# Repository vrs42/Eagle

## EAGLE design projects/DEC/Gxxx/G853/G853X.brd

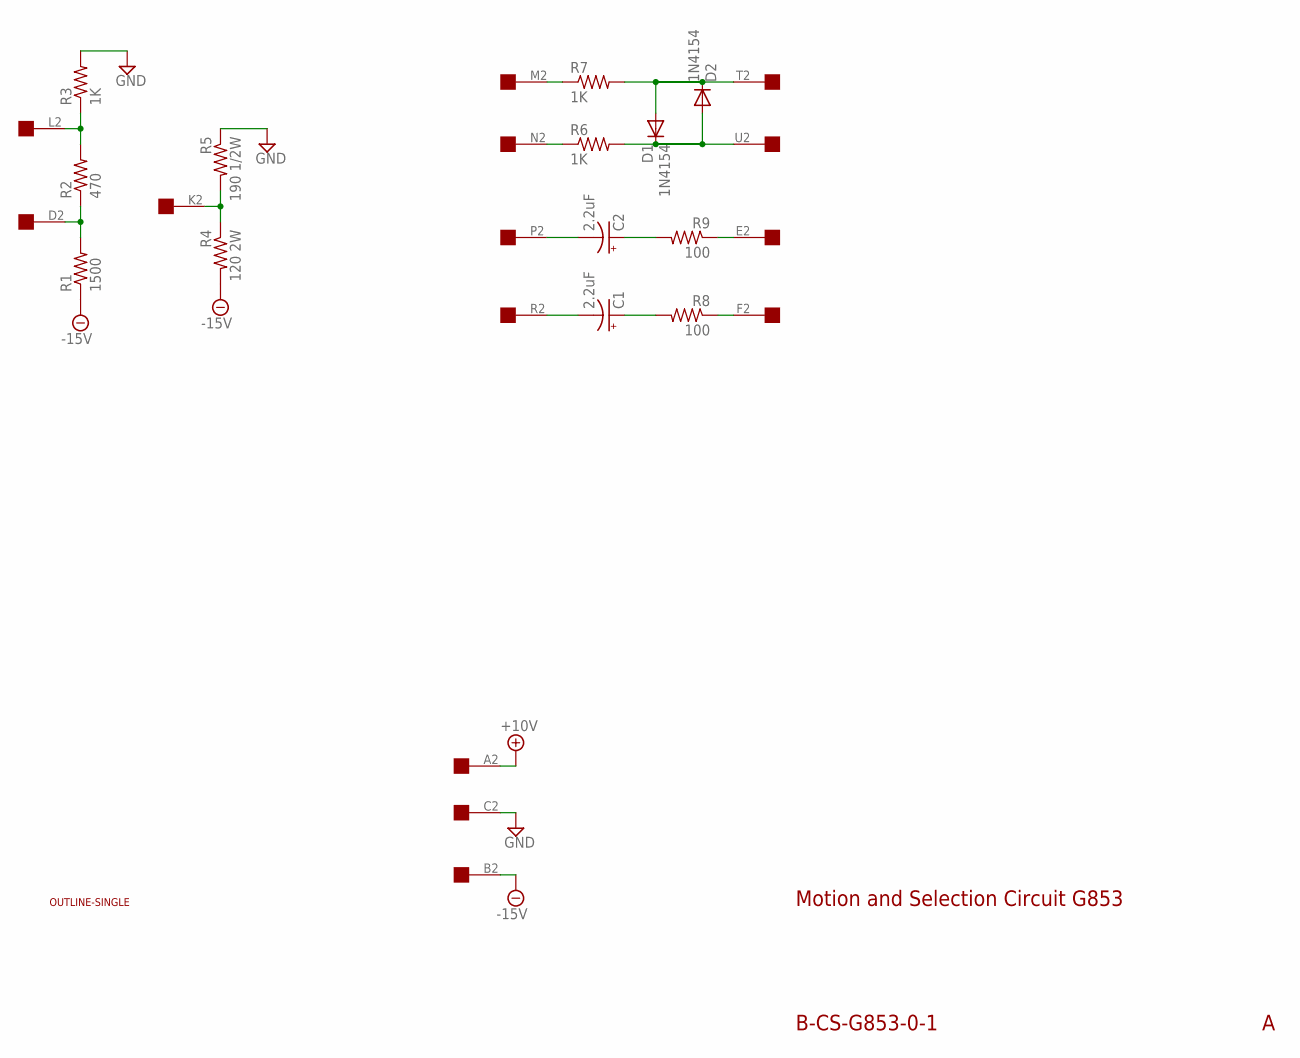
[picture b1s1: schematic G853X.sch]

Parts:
C1, C2: 2.2uF; E15-5
D1, D2: 1N4154; DO35-10
R1: 1500; 0207/10
R2: 470; 0207/10
R3, R6, R7: 1K; 0207/10
R4: 120 2W; P0817/22
R5: 190 1/2W; 0309/12
R8, R9: 100; 0207/10
U$1: OUTLINE-SINGLE; SINGLE
U$2: EDGE-1; EDGE-CON1

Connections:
+10V: U$2.A2
-15V: R1.1, R4.2, U$2.B2
GND: R3.2, R5.1, U$2.C2
unnamed: C1.-, U$2.R2
unnamed: C1.+, R8.2
unnamed: R1.2, R2.1, U$2.D2
unnamed: R6.1, U$2.N2
unnamed: R7.1, U$2.M2
unnamed: D1.A, D2.C, R7.2, U$2.T2
unnamed: D1.C, D2.A, R6.2, U$2.U2
unnamed: R2.2, R3.1, U$2.L2
unnamed: C2.+, R9.2
unnamed: C2.-, U$2.P2
unnamed: R8.1, U$2.F2
unnamed: R9.1, U$2.E2
unnamed: R4.1, R5.2, U$2.K2

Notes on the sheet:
Motion and Selection Circuit G853
B-CS-G853-0-1

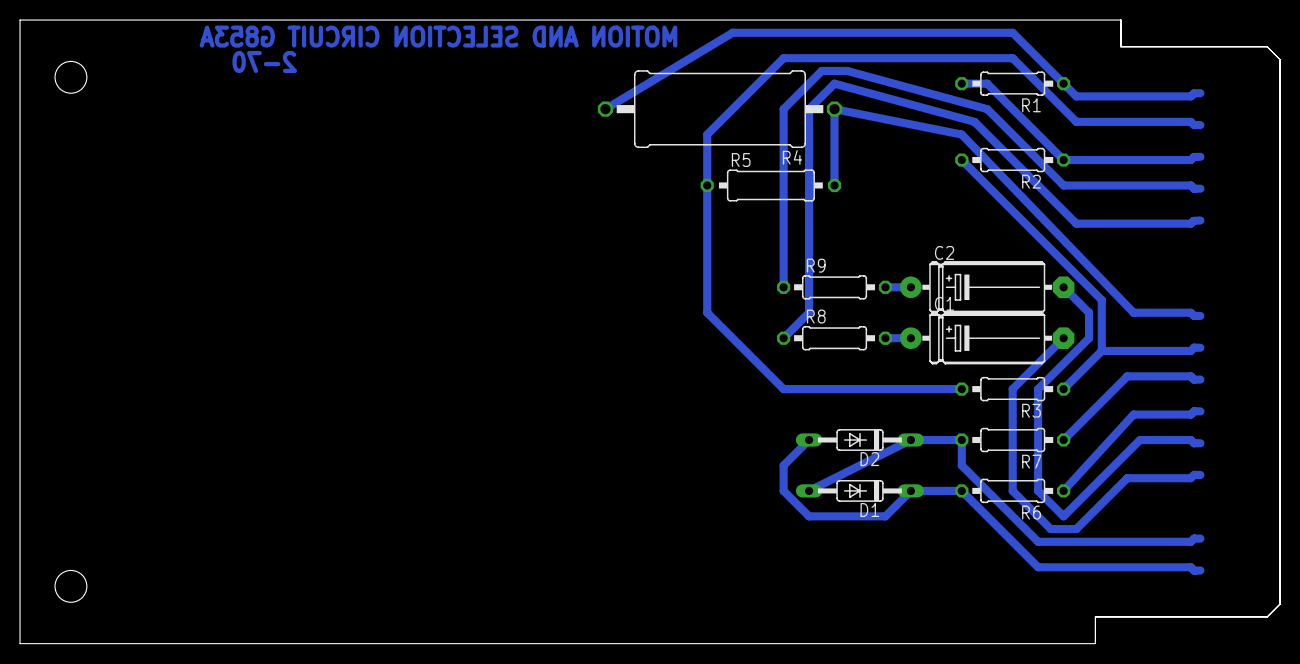
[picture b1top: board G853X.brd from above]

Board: 2 copper layers, 125.7 x 62.2 mm, 15 parts (0 on the bottom side), 15 nets.

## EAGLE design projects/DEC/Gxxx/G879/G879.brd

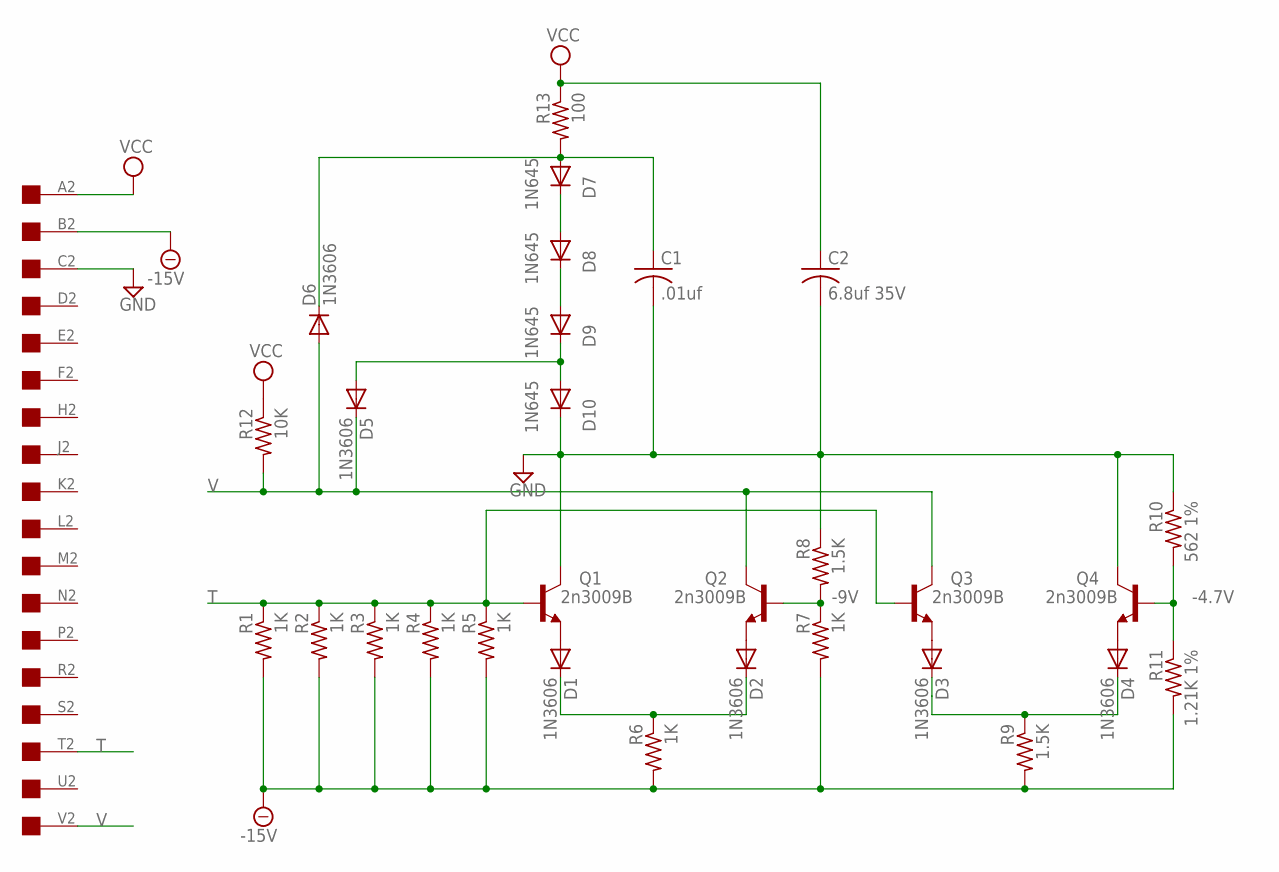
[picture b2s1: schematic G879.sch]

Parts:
C1: .01uf; C050-025X075
C2: 6.8uf 35V; C102-054X133
D1, D2, D3, D4, D5, D6: 1N3606; DO41-10
D7, D8, D9, D10: 1N645; DO41-10
Q1, Q2, Q3, Q4: 2n3009B; TO39
R1, R2, R3, R4, R5, R6, R7: 1K; 0207/10
R8, R9: 1.5K; 0207/10
R10: 562 1%; 0207/10
R11: 1.21K 1%; 0207/10
R12: 10K; 0207/10
R13: 100; 0207/10
U$5: ONE-SIDED

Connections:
-4.7V: Q4.2 (B), R10.2, R11.1
-9V: Q2.2 (B), R7.1, R8.2
-15V: R1.2, R2.2, R3.2, R4.2, R5.2, R6.2, R7.2, R9.2, R11.2, U$5.B2
GND: C1.2, C2.2, D10.C, Q1.3 (C), Q4.3 (C), R8.1, R10.1, U$5.C2
unnamed: D1.A, Q1.1 (E)
unnamed: D3.C, D4.C, R9.1
unnamed: D2.A, Q2.1 (E)
unnamed: D4.A, Q4.1 (E)
unnamed: D5.A, D9.C, D10.A
unnamed: D1.C, D2.C, R6.1
unnamed: D8.C, D9.A
unnamed: D3.A, Q3.1 (E)
unnamed: D7.C, D8.A
unnamed: C1.1, D6.C, D7.A, R13.2
T: Q1.2 (B), Q3.2 (B), R1.1, R2.1, R3.1, R4.1, R5.1, U$5.T2
V: D5.C, D6.A, Q2.3 (C), Q3.3 (C), R12.2, U$5.V2
VCC: C2.1, R12.1, R13.1, U$5.A2

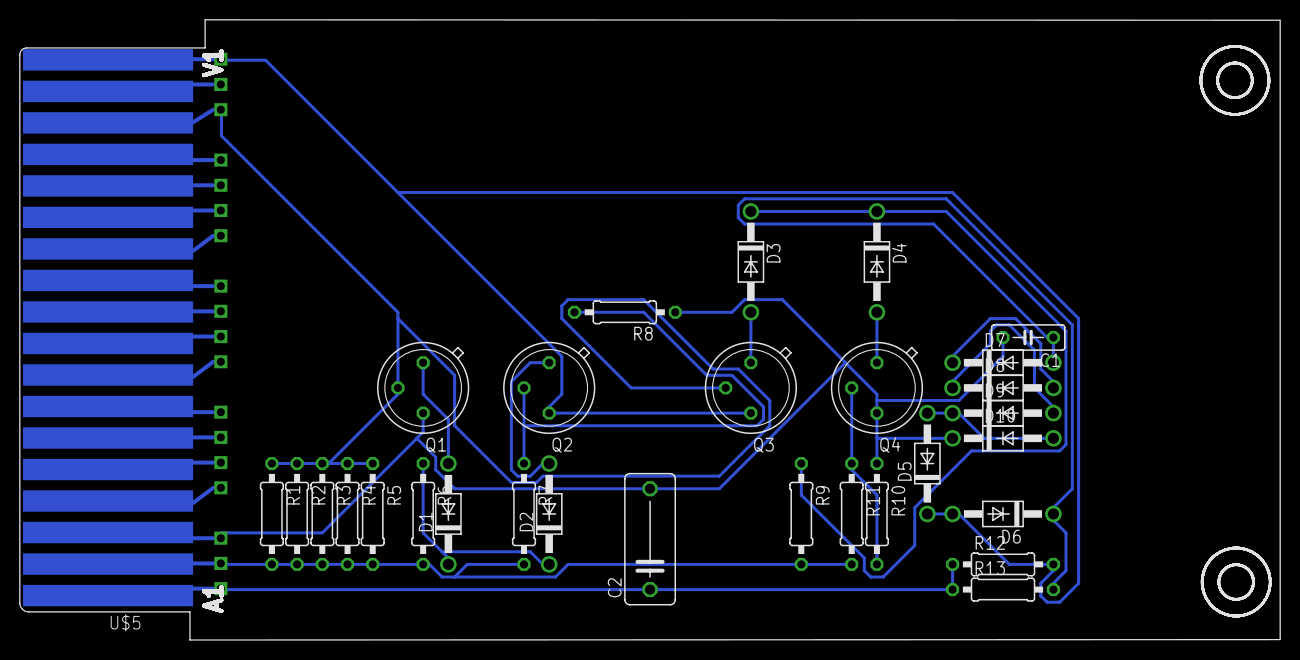
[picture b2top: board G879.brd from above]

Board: 2 copper layers, 127.0 x 62.5 mm, 32 parts (0 on the bottom side), 17 nets.

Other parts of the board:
U$2, U$3: 3,3

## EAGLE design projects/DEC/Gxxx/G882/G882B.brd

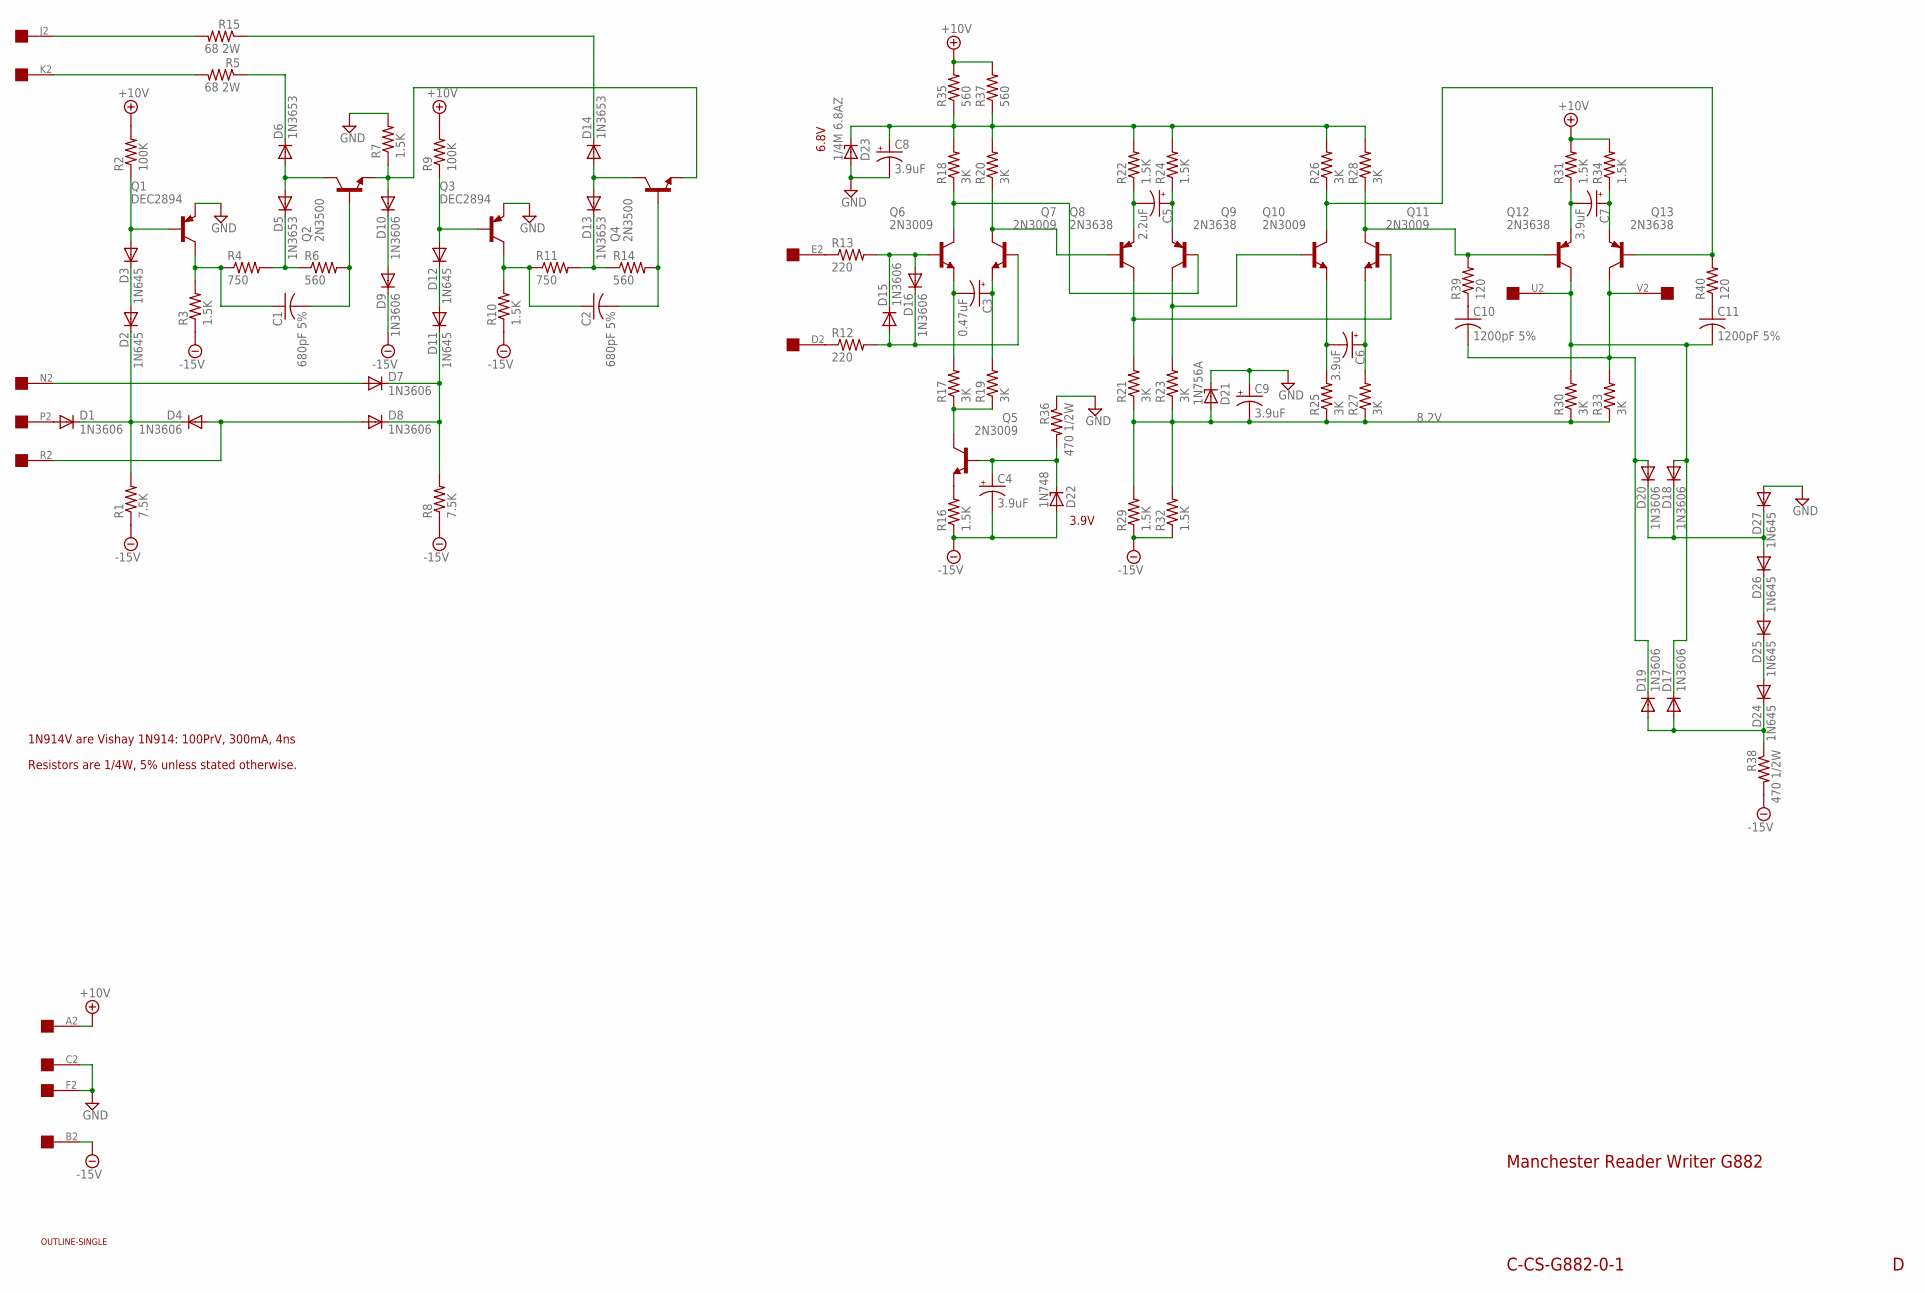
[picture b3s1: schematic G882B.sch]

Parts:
C1, C2: 680pF 5%; C050-025X075
C3: 0.47uF; E12-4
C4, C6, C7, C8, C9: 3.9uF; E12-4
C5: 2.2uF; E12-4
C10, C11: 1200pF 5%; C050-025X075
D1, D4, D7, D8, D9, D10, D15, D16, D17, D18, D19, D20: 1N3606; DO35-10
D2, D3, D11, D12, D24, D25, D26, D27: 1N645; DO35-10
D5, D6, D13, D14: 1N3653; DO35-10
D21: 1N756A; DO35Z10
D22: 1N748; DO35Z10
D23: 1/4M 6.8AZ; DO35Z10
Q1, Q3: DEC2894; TO39
Q2, Q4: 2N3500; TO5
Q5, Q6, Q7, Q10, Q11: 2N3009; TO5
Q8, Q9, Q12, Q13: 2N3638; TO39
R1, R8: 7.5K; 0207/10
R2, R9: 100K; 0207/10
R3, R7, R10, R16, R22, R24, R29, R31, R32, R34: 1.5K; 0207/10
R4, R11: 750; 0207/10
R5, R15: 68 2W; P0817/22
R6, R14, R35, R37: 560; 0207/10
R12, R13: 220; 0207/10
R17, R18, R19, R20, R21, R23, R25, R26, R27, R28, R30, R33: 3K; 0207/10
R36, R38: 470 1/2W; 0309/12
R39, R40: 120; 0207/10
U$1: OUTLINE-SINGLE; SINGLE
U$2: EDGE-1; EDGE-CON1

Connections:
8.2V: C9.-, D21.A, R21.1, R23.1, R25.1, R27.1, R29.2, R30.1, R32.2, R33.1
+10V: R2.2, R9.2, R31.2, R34.2, R35.2, R37.2, U$2.A2
-15V: C4.-, D9.C, D22.A, R1.1, R3.1, R8.1, R10.1, R16.1, R29.1, R32.1, R38.2, U$2.B2
GND: C8.-, C9.+, D21.C, D23.A, D27.A, Q1.1 (E), Q3.1 (E), R7.2, R36.1, U$2.C2, U$2.F2
unnamed: D1.A, U$2.P2
unnamed: D11.A, D12.C
unnamed: D4.A, D8.A, U$2.R2
unnamed: D7.A, U$2.N2
unnamed: C1.1, Q1.3 (C), R3.2, R4.1
unnamed: D1.C, D2.C, D4.C, R1.2
unnamed: D5.C, R4.2, R6.1
unnamed: D7.C, D8.C, D11.C, R8.2
unnamed: D12.A, Q3.2 (B), R9.1
unnamed: D2.A, D3.C
unnamed: D5.A, D6.A, Q2.3 (C)
unnamed: R5.2, U$2.K2
unnamed: D6.C, R5.1
unnamed: D3.A, Q1.2 (B), R2.1
unnamed: C1.2, Q2.2 (B), R6.2
unnamed: D10.A, Q2.1 (E), Q4.1 (E), R7.1
unnamed: D9.A, D10.C
unnamed: R15.2, U$2.J2
unnamed: C2.1, Q3.3 (C), R10.2, R11.1
unnamed: D13.C, R11.2, R14.1
unnamed: D13.A, D14.A, Q4.3 (C)
unnamed: D14.C, R15.1
unnamed: C2.2, Q4.2 (B), R14.2
unnamed: R13.1, U$2.E2
unnamed: R12.1, U$2.D2
unnamed: D15.A, D16.C, Q7.2 (B), R12.2
unnamed: D15.C, D16.A, Q6.2 (B), R13.2
unnamed: C3.-, Q6.1 (E), R17.2
unnamed: C3.+, Q7.1 (E), R19.2
unnamed: Q5.3 (C), R17.1, R19.1
unnamed: Q5.1 (E), R16.2
unnamed: C4.+, D22.C, Q5.2 (B), R36.2
unnamed: C8.+, D23.C, R18.2, R20.2, R22.2, R24.2, R26.2, R28.2, R35.1, R37.1
unnamed: C5.-, Q8.1 (E), R22.1
unnamed: Q7.3 (C), Q8.2 (B), R20.1
unnamed: Q6.3 (C), Q9.2 (B), R18.1
unnamed: C5.+, Q9.1 (E), R24.1
unnamed: Q8.3 (C), Q11.2 (B), R21.2
unnamed: Q9.3 (C), Q10.2 (B), R23.2
unnamed: C6.-, Q10.1 (E), R25.2
unnamed: C6.+, Q11.1 (E), R27.2
unnamed: Q11.3 (C), Q12.2 (B), R28.1, R39.2
unnamed: Q10.3 (C), Q13.2 (B), R26.1, R40.2
unnamed: C7.-, Q12.1 (E), R31.1
unnamed: C7.+, Q13.1 (E), R34.1
unnamed: C11.2, D17.C, D18.A, Q12.3 (C), R30.2, U$2.U2
unnamed: C10.2, D19.C, D20.A, Q13.3 (C), R33.2, U$2.V2
unnamed: D17.A, D19.A, D24.C, R38.1
unnamed: D24.A, D25.C
unnamed: D25.A, D26.C
unnamed: D18.C, D20.C, D26.A, D27.C
unnamed: C10.1, R39.1
unnamed: C11.1, R40.1

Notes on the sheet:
Manchester Reader Writer G882
C-CS-G882-0-1
1N914V are Vishay 1N914: 100PrV, 300mA, 4ns
Resistors are 1/4W, 5% unless stated otherwise.
3.9V
6.8V

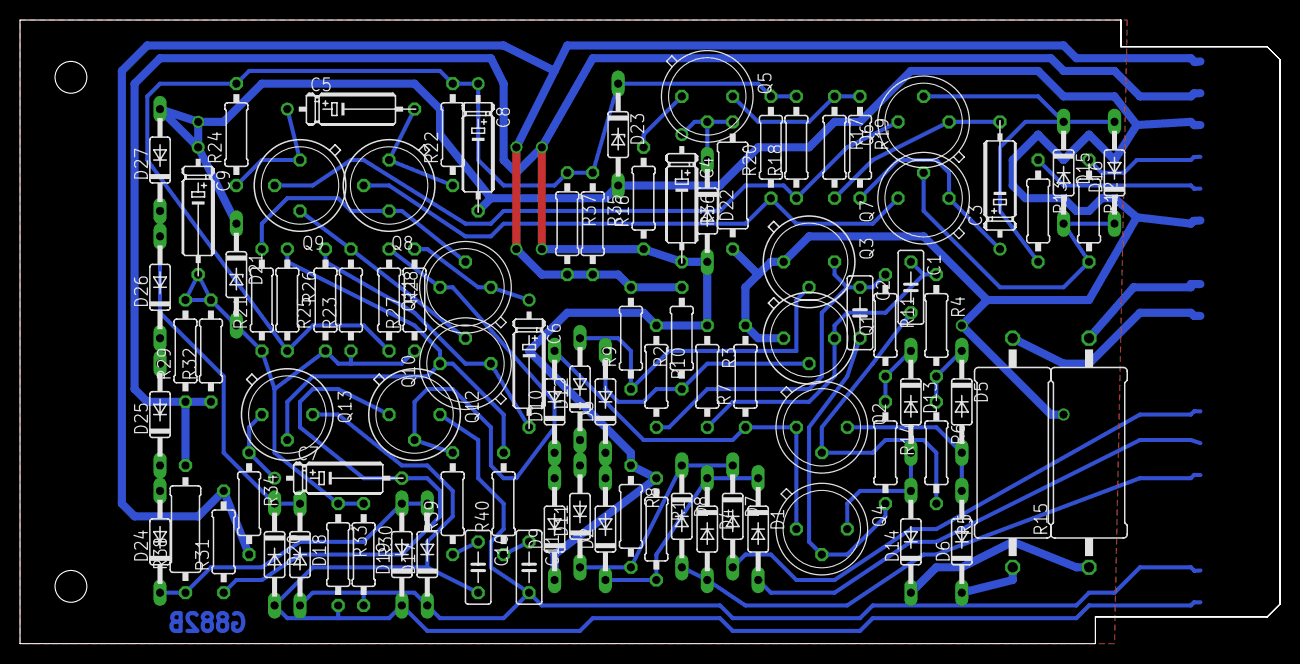
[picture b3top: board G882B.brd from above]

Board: 2 copper layers, 125.7 x 62.2 mm, 93 parts (0 on the bottom side), 57 nets.

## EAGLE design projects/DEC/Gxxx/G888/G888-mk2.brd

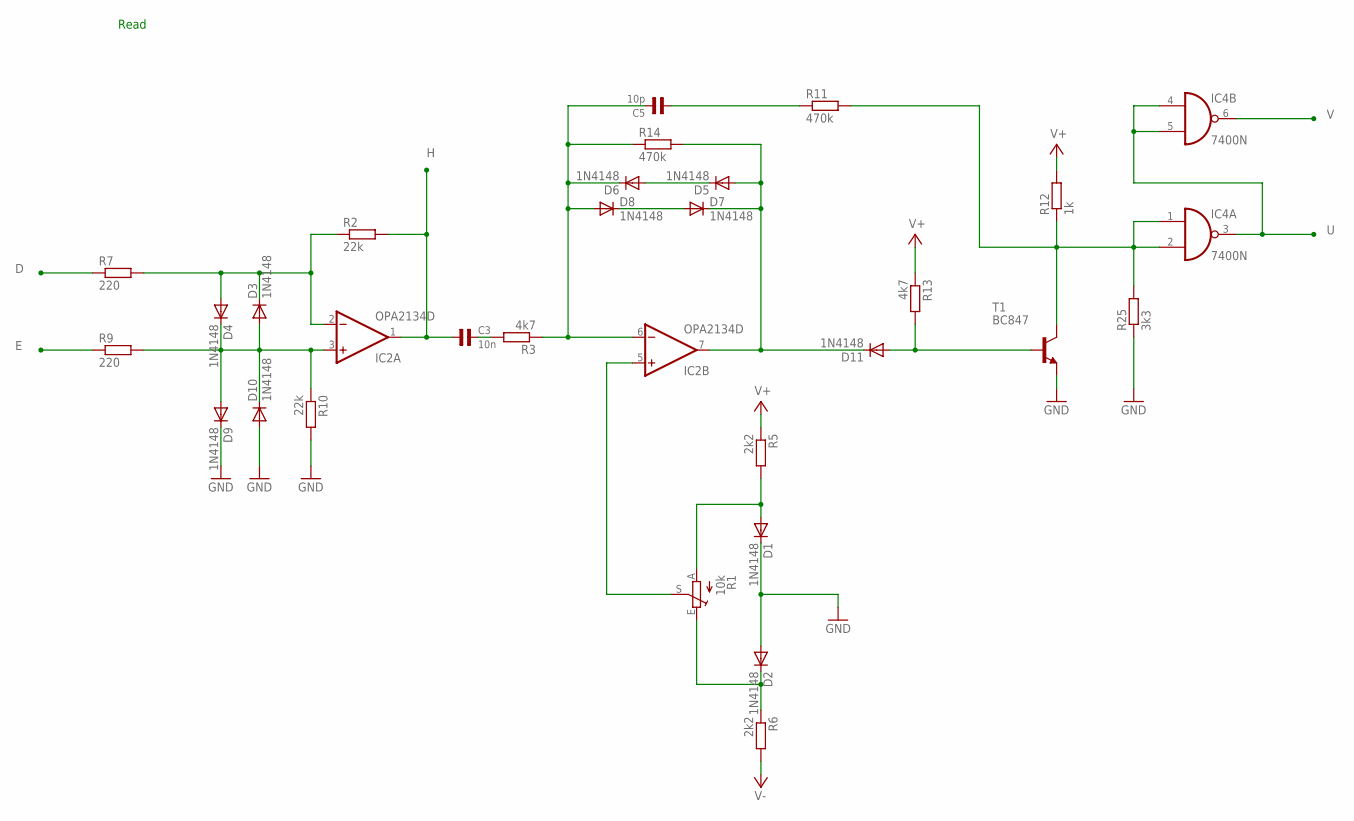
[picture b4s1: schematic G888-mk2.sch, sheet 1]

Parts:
C3: 10n; 0805
C5: 10p; 0805
D1, D2, D3, D4, D5, D6, D7, D8, D9, D10, D11: 1N4148; SOD123
IC2: OPA2134D; SOIC8
IC4: 7400N; DIL14
R1: 10k; SP19L
R2, R10: 22k; R0805
R3, R13: 4k7; R0805
R5, R6: 2k2; R0805
R7, R9: 220; R0805
R11, R14: 470k; R0805
R12: 1k; R0805
R25: 3k3; R0805
T1: BC847; SOT23

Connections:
D: R7.1; also elsewhere on the board
E: R9.1; also elsewhere on the board
GND: D1.C, D2.A, D9.C, D10.A, R10.2, R25.1, T1.2 (E); also elsewhere on the board
H: C3.1, IC2.1 (OUT), R2.2; also elsewhere on the board
unnamed: D3.C, D4.A, IC2.2 (-IN), R2.1, R7.2
unnamed: D5.C, D6.A
unnamed: C5.2, D6.C, D8.A, IC2.6 (-IN), R3.1, R14.1
unnamed: D1.A, R1.A, R5.2
unnamed: D5.A, D7.C, D11.C, IC2.7 (OUT), R14.2
unnamed: D11.A, R13.2, T1.1 (B)
unnamed: C5.1, R11.1
unnamed: D7.A, D8.C
unnamed: D2.C, R1.E, R6.1
unnamed: C3.2, R3.2
unnamed: IC2.5 (+IN), R1.S
unnamed: D3.A, D4.C, D9.A, D10.C, IC2.3 (+IN), R9.2, R10.1
TIMING: IC4.1 (I0), IC4.2 (I1), R11.2, R12.1, R25.2, T1.3 (C)
U: IC4.3 (O), IC4.4 (I0), IC4.5 (I1); also elsewhere on the board
V: IC4.6 (O); also elsewhere on the board
V+: R5.1, R12.2, R13.1; also elsewhere on the board
V-: R6.2; also elsewhere on the board

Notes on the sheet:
Read

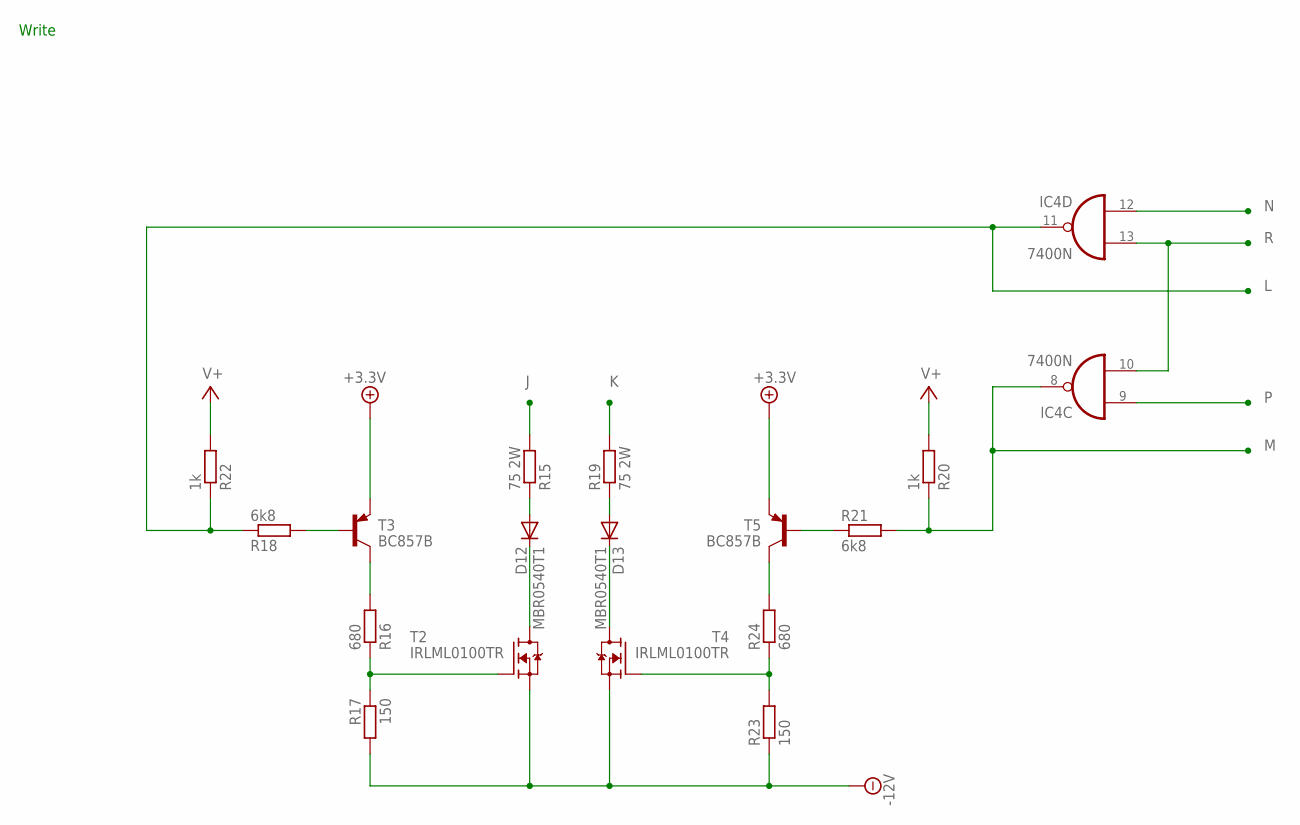
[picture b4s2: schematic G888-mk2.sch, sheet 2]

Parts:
D12, D13: MBR0540T1; SOD123
IC4: 7400N; DIL14
R15, R19: 75 2W; R2512
R16, R24: 680; R0805
R17, R23: 150; R0805
R18, R21: 6k8; R0805
R20, R22: 1k; R0805
T2, T4: IRLML0100TR; SOT23
T3, T5: BC857B; SOT23

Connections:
+3.3V: T3.2 (E), T5.2 (E); also elsewhere on the board
-12V: R17.2, R23.1, T2.2 (S), T4.2 (S); also elsewhere on the board
J: R15.2; also elsewhere on the board
K: R19.2; also elsewhere on the board
L: IC4.11 (O), R18.1, R22.1; also elsewhere on the board
M: IC4.8 (O), R20.1, R21.2; also elsewhere on the board
N: IC4.12 (I0); also elsewhere on the board
unnamed: R21.1, T5.1 (B)
unnamed: D13.A, R19.1
unnamed: D13.C, T4.3 (D)
unnamed: R24.2, T5.3 (C)
unnamed: R23.2, R24.1, T4.1 (G)
unnamed: R18.2, T3.1 (B)
unnamed: D12.A, R15.1
unnamed: D12.C, T2.3 (D)
unnamed: R16.2, T3.3 (C)
unnamed: R16.1, R17.1, T2.1 (G)
P: IC4.9 (I0); also elsewhere on the board
R: IC4.10 (I1), IC4.13 (I1); also elsewhere on the board
V+: R20.2, R22.2; also elsewhere on the board

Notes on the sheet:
Write

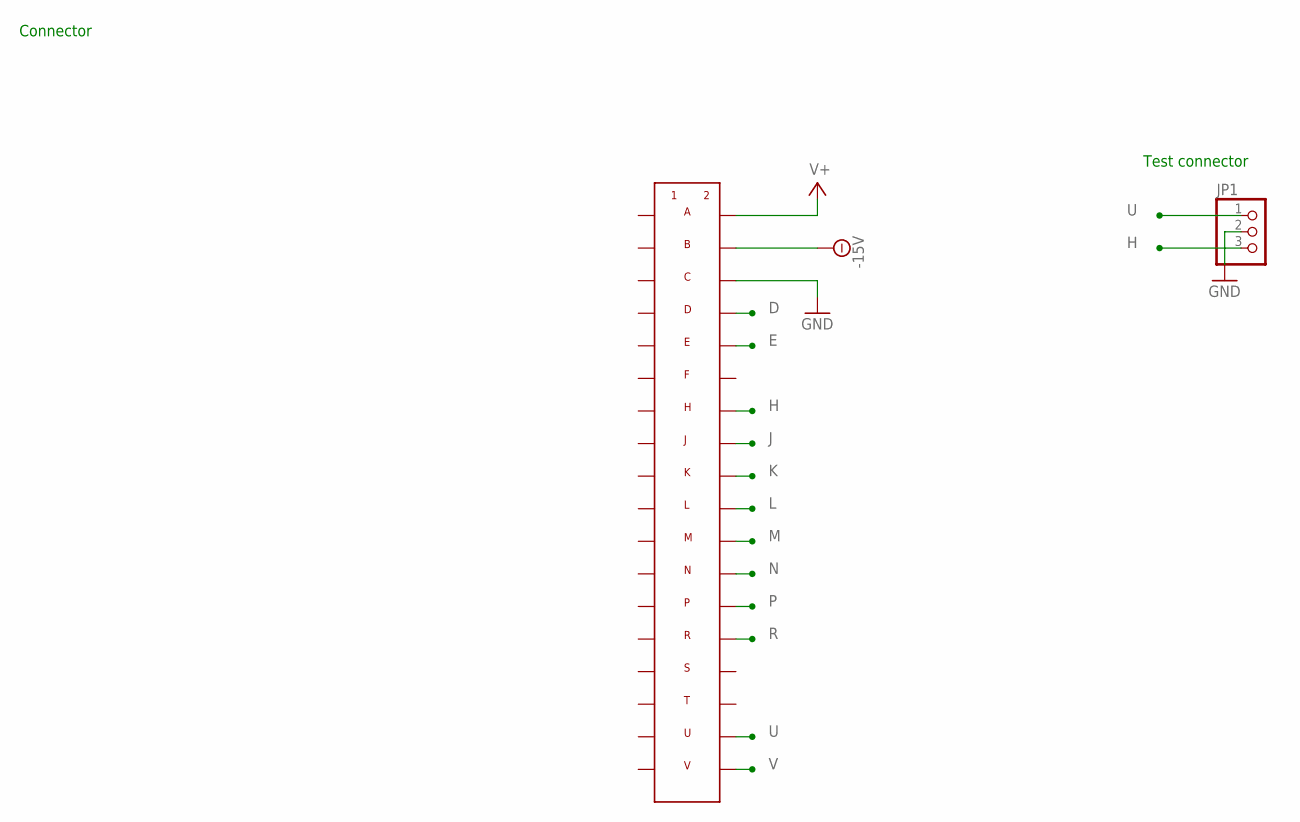
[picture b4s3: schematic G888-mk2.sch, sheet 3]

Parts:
CON1: FLIPCHIP_1NORMAL; FLIPCHIP-1
JP1: PINHD-1X3/90; 1X03/90

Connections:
-15V: CON1.B2; also elsewhere on the board
D: CON1.D2; also elsewhere on the board
E: CON1.E2; also elsewhere on the board
GND: CON1.C2, JP1.2; also elsewhere on the board
H: CON1.H2 (G2), JP1.3; also elsewhere on the board
J: CON1.J2; also elsewhere on the board
K: CON1.K2; also elsewhere on the board
L: CON1.L2; also elsewhere on the board
M: CON1.M2; also elsewhere on the board
N: CON1.N2; also elsewhere on the board
P: CON1.P2; also elsewhere on the board
R: CON1.R2; also elsewhere on the board
U: CON1.U2, JP1.1; also elsewhere on the board
V: CON1.V2; also elsewhere on the board
V+: CON1.A2; also elsewhere on the board

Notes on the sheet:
Connector
Test connector

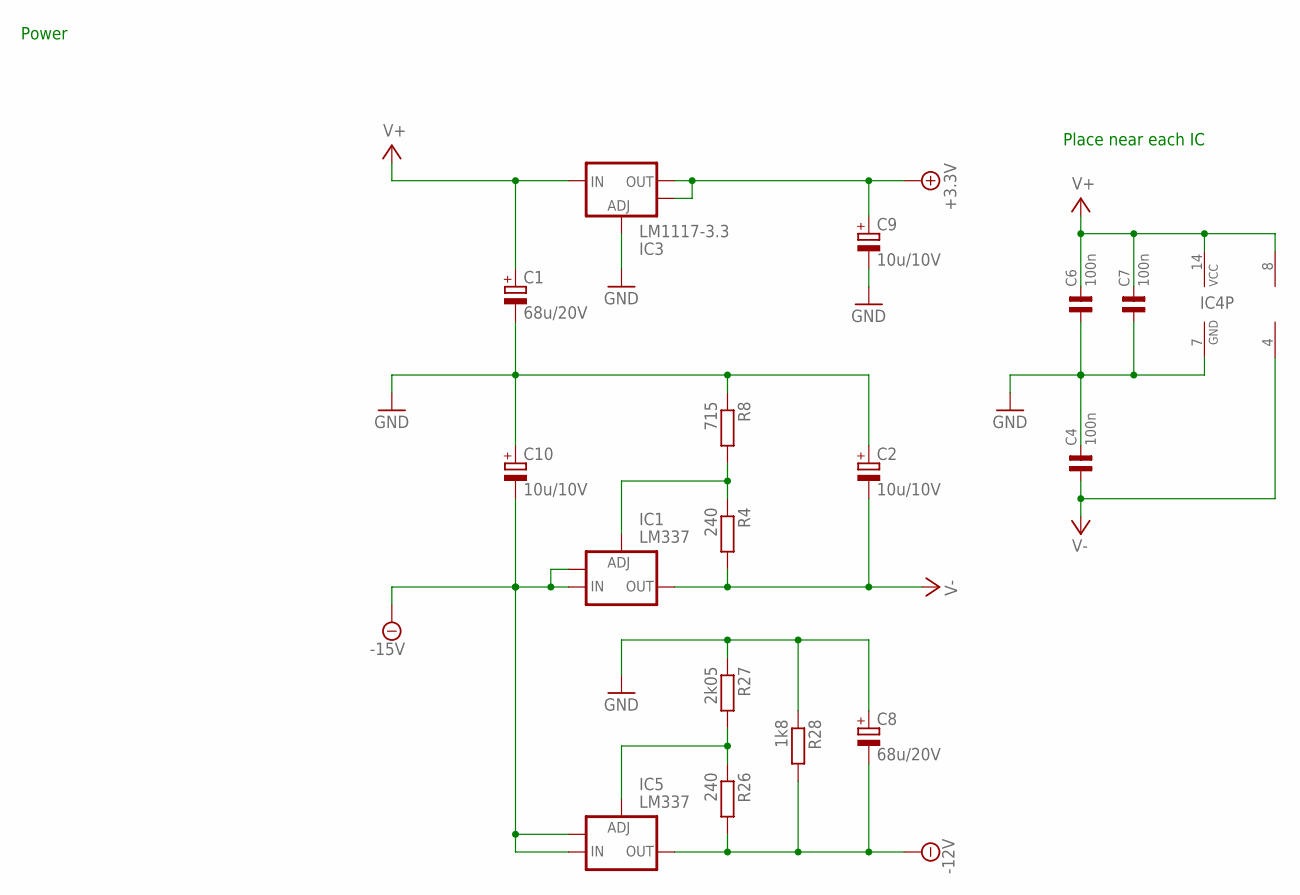
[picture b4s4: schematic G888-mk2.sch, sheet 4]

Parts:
C1, C8: 68u/20V; SMC_D
C2, C9, C10: 10u/10V; SMC_C
C4, C6, C7: 100n; 0805
IC1, IC5: LM337; SOT223
IC2: OPA2134D; SOIC8
IC3: LM1117-3.3; SOT223
IC4: 7400N; DIL14
R4, R26: 240; R0805
R8: 715; R0805
R27: 2k05; R0805
R28: 1k8; R0805

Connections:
+3.3V: C9.+, IC3.2 (OUT), IC3.4 (OUT_TAB); also elsewhere on the board
-12V: C8.-, IC5.3 (OUT), R26.2, R28.2; also elsewhere on the board
-15V: C10.-, IC1.2 (IN), IC1.4 (IN_TAB), IC5.2 (IN), IC5.4 (IN_TAB); also elsewhere on the board
GND: C1.-, C2.+, C4.2, C6.1, C7.1, C8.+, C9.-, C10.+, IC3.1 (GND), IC4.7 (GND), R8.1, R27.1, R28.1; also elsewhere on the board
unnamed: IC5.1 (ADJ), R26.1, R27.2
unnamed: IC1.1 (ADJ), R4.1, R8.2
V+: C1.+, C6.2, C7.2, IC2.8 (V+), IC3.3 (IN), IC4.14 (VCC); also elsewhere on the board
V-: C2.-, C4.1, IC1.3 (OUT), IC2.4 (V-), R4.2; also elsewhere on the board

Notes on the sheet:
Power
Place near each IC

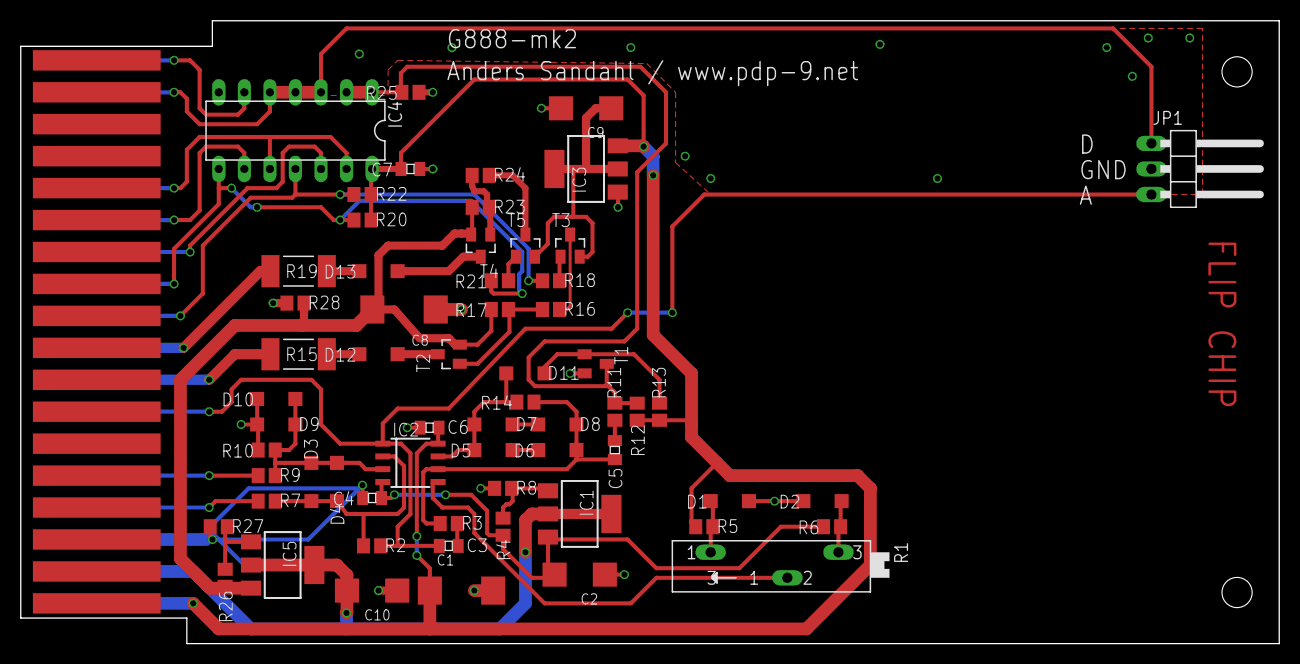
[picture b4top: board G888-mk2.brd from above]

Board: 2 copper layers, 125.1 x 61.9 mm, 63 parts (0 on the bottom side), 43 nets.

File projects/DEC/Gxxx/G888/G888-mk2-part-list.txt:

Partlist

Exported from G888-mk2.sch at 2020-01-14 21:51:39

EAGLE Version 5.7.0 Copyright (c) 1988-2010 CadSoft

Part     Value            Device           Package    Library    Sheet

C1       68u/20V          CPOL-EUSMCD      SMC_D      anders     4
C2       10u/10V          CPOL-EUSMCC      SMC_C      anders     4
C3       10n              C0805            0805       capsmd     1
C4       100n             C0805            0805       capsmd     4
C5       10p              C0805            0805       capsmd     1
C6       100n             C0805            0805       capsmd     4
C7       100n             C0805            0805       capsmd     4
C8       68u/20V          CPOL-EUSMCD      SMC_D      anders     4
C9       10u/10V          CPOL-EUSMCC      SMC_C      anders     4
C10      10u/10V          CPOL-EUSMCC      SMC_C      anders     4
CON1     FLIPCHIP_1NORMAL FLIPCHIP_1NORMAL FLIPCHIP-1 anders     3
D1       1N4148           1N4148-Y         SOD123     diode      1
D2       1N4148           1N4148-Y         SOD123     diode      1
D3       1N4148           1N4148-Y         SOD123     diode      1
D4       1N4148           1N4148-Y         SOD123     diode      1
D5       1N4148           1N4148-Y         SOD123     diode      1
D6       1N4148           1N4148-Y         SOD123     diode      1
D7       1N4148           1N4148-Y         SOD123     diode      1
D8       1N4148           1N4148-Y         SOD123     diode      1
D9       1N4148           1N4148-Y         SOD123     diode      1
D10      1N4148           1N4148-Y         SOD123     diode      1
D11      1N4148           1N4148-Y         SOD123     diode      1
D12      MBR0540T1        MBR0540T1        SOD123     anders     2
D13      MBR0540T1        MBR0540T1        SOD123     anders     2
IC1      LM337            LM337-SOT223     SOT223     v-reg      4
IC2      OPA2134D         OPA2134D         SOIC8      linear     1
IC3      LM1117-3.3       LM1117-3.3       SOT223     v-reg      4
IC4      7400N            7400N            DIL14      74xx-eu    1
IC5      LM337            LM337-SOT223     SOT223     v-reg      4
JP1                       PINHD-1X3/90     1X03/90    pinhead    3
R1       10k              TRIM_EU-SP19L    SP19L      anders     1
R2       22k              R-EU_R0805       R0805      anders     1
R3       4k7              R-EU_R0805       R0805      anders     1
R4       240              R-EU_R0805       R0805      anders     4
R5       2k2              R-EU_R0805       R0805      anders     1
R6       2k2              R-EU_R0805       R0805      anders     1
R7       220              R-EU_R0805       R0805      anders     1
R8       715              R-EU_R0805       R0805      anders     4
R9       220              R-EU_R0805       R0805      anders     1
R10      22k              R-EU_R0805       R0805      anders     1
R11      470k             R-EU_R0805       R0805      anders     1
R12      1k               R-EU_R0805       R0805      anders     1
R13      4k7              R-EU_R0805       R0805      anders     1
R14      470k             R-EU_R0805       R0805      anders     1
R15      75 2W            R-EU_R2512       R2512      anders     2
R16      680              R-EU_R0805       R0805      anders     2
R17      150              R-EU_R0805       R0805      anders     2
R18      6k8              R-EU_R0805       R0805      anders     2
R19      75 2W            R-EU_R2512       R2512      anders     2
R20      1k               R-EU_R0805       R0805      anders     2
R21      6k8              R-EU_R0805       R0805      anders     2
R22      1k               R-EU_R0805       R0805      anders     2
R23      150              R-EU_R0805       R0805      anders     2
R24      680              R-EU_R0805       R0805      anders     2
R25      3k3              R-EU_R0805       R0805      anders     1
R26      240              R-EU_R0805       R0805      anders     4
R27      2k05             R-EU_R0805       R0805      anders     4
R28      1k8              R-EU_R0805       R0805      anders     4
T1       BC847            BC847            SOT23      transistor 1
T2       IRLML0100TR      IRLML0100TR      SOT23      anders     2
T3       BC857B           BC857B           SOT23      anders     2
T4       IRLML0100TR      IRLML0100TR      SOT23      anders     2
T5       BC857B           BC857B           SOT23      anders     2
